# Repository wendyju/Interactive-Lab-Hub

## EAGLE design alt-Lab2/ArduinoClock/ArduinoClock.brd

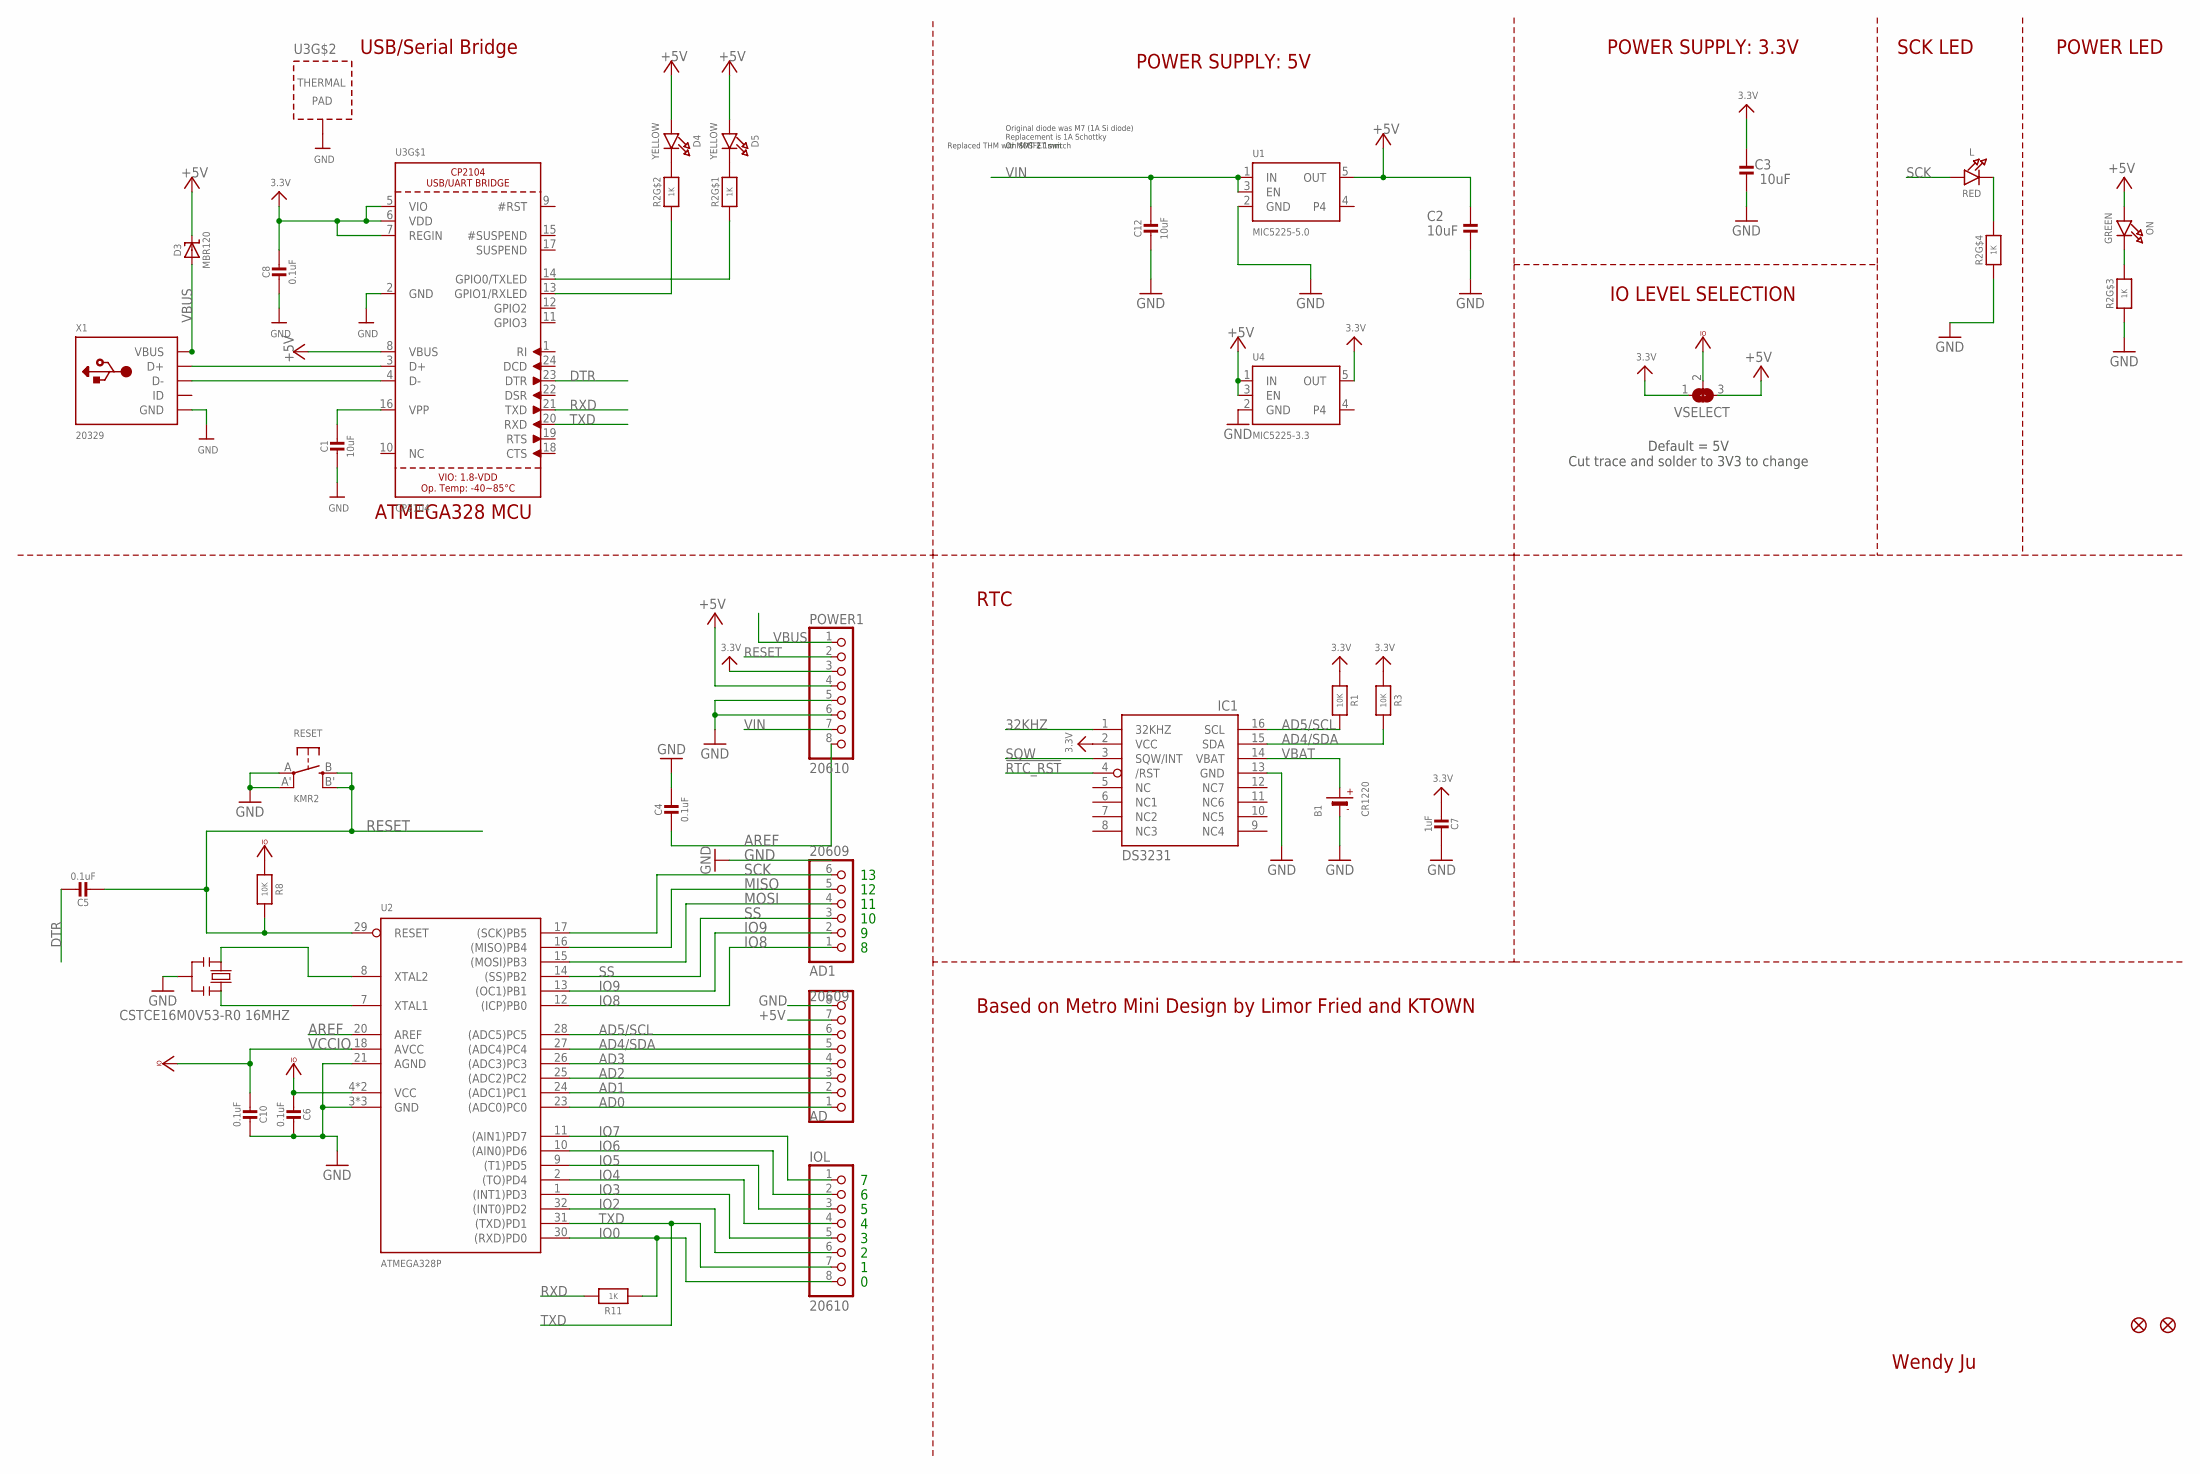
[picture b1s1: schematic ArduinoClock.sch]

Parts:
AD: 20609; 1X08_ROUND
AD1: 20609; 1X06_ROUND
B1: CR1220
C1, C2, C3, C12: 10uF; 0805-NO
C4, C6, C8, C10: 0.1uF; 0805-NO
C5: 0.1uF; _0805MP
C7: 1uF; 0805-NO
D3: MBR120; SOD-123
D4, D5: YELLOW; CHIPLED_0805_NOOUTLINE
FD1, FD2: FIDUCIAL""; FIDUCIAL_1MM
IC1: DS3231/SO; SO16W
IOL: 20610; 1X08_ROUND
L: RED; CHIPLED_0805_NOOUTLINE
ON: GREEN; CHIPLED_0805_NOOUTLINE
POWER1: 20610; 1X08_ROUND_70
R1, R3, R8: 10K; 0805-NO
R2: 1K; RESPACK_4X0603
R11: 1K; 0805-NO
RESET: KMR2; BTN_KMR2_4.6X2.8
U1: MIC5225-5.0; SOT23-5
U2: ATMEGA328P; MLF32-TH
U3: CP2104; QFN24_4MM_SMSC
U4: MIC5225-3.3; SOT23-5
VSELECT: SOLDERJUMPER_2WAY; SOLDERJUMPER_2WAY_OPEN_NOPASTE
X1: 20329; 4UCONN_20329_V2
Y2: CSTCE16M0V53-R0 16MHZ; RESONATOR

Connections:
3.3V: C3.2, C7.2, C8.1, IC1.2 (VCC), POWER1.3, R1.1, R3.1, U3.5 (VIO), U3.6 (VDD), U3.7 (REGIN), U4.5 (OUT), VSELECT.1
32KHZ: IC1.1 (32KHZ)
!RTC_RST: IC1.4 (/RST)
+5V: AD.7, C2.2, D3.C, D4.A, D5.A, ON.A, POWER1.4, U1.5 (OUT), U3.8 (VBUS), U4.1 (IN), U4.3 (EN), VSELECT.3
AD0: AD.1, U2.23 ((ADC0)PC0)
AD1: AD.2, U2.24 ((ADC1)PC1)
AD2: AD.3, U2.25 ((ADC2)PC2)
AD3: AD.4, U2.26 ((ADC3)PC3)
AD4/SDA: AD.5, IC1.15 (SDA), R3.2, U2.27 ((ADC4)PC4)
AD5/SCL: AD.6, IC1.16 (SCL), R1.2, U2.28 ((ADC5)PC5)
AREF: C4.2, POWER1.8, U2.20 (AREF)
DTR: C5.1, U3.23 (DTR)
GND: AD.8, B1.-, C1.2, C2.1, C3.1, C4.1, C6.1, C7.1, C8.2, C10.1, C12.2, IC1.13 (GND), POWER1.5, POWER1.6, R2.3 (1), R2.4 (1), RESET.A, RESET.A' (P1), U1.2 (GND), U2.3 (GND), U2.5 (GND), U2.21 (AGND), U2.TH (GND), U3.2 (GND), U3.THERM (TP), U4.2 (GND), X1.BASE@1 (GND), X1.BASE@2 (GND), X1.GND, X1.SPRT@1 (GND), X1.SPRT@2 (GND), X1.SPRT@3 (GND), X1.SPRT@4 (GND), Y2.2
IO0: IOL.8, R11.1, U2.30 ((RXD)PD0)
IO2: IOL.6, U2.32 ((INT0)PD2)
IO3: IOL.5, U2.1 ((INT1)PD3)
IO4: IOL.4, U2.2 ((TO)PD4)
IO5: IOL.3, U2.9 ((T1)PD5)
IO6: IOL.2, U2.10 ((AIN0)PD6)
IO7: IOL.1, U2.11 ((AIN1)PD7)
IO8: AD1.1, U2.12 ((ICP)PB0)
IO9: AD1.2, U2.13 ((OC1)PB1)
MISO: AD1.5, U2.16 ((MISO)PB4)
MOSI: AD1.4, U2.15 ((MOSI)PB3)
unnamed: L.C, R2.5 (2)
unnamed: ON.C, R2.6 (2)
unnamed: R2.1, U3.14 (GPIO0/TXLED)
unnamed: D4.C, R2.7 (2)
unnamed: D5.C, R2.8 (2)
unnamed: U3.3 (D+), X1.D+
unnamed: U3.4 (D-), X1.D-
unnamed: C1.1, U3.16 (VPP)
unnamed: R2.2 (1), U3.13 (GPIO1/RXLED)
RESET: C5.2, POWER1.2, R8.1, RESET.B (S), RESET.B' (S1), U2.29 (RESET)
RXD: R11.2, U3.21 (TXD)
SCK: AD1.6, L.A, U2.17 ((SCK)PB5)
SQW: IC1.3 (SQW/INT)
SS: AD1.3, U2.14 ((SS)PB2)
TXD: IOL.7, U2.31 ((TXD)PD1), U3.20 (RXD)
VBAT: B1.+$1 (+), IC1.14 (VBAT)
VBUS: D3.A, POWER1.1, X1.VBUS
VCCIO: C6.2, C10.2, R8.2, U2.4 (VCC), U2.6 (VCC), U2.18 (AVCC), VSELECT.2
VIN: C12.1, POWER1.7, U1.1 (IN), U1.3 (EN)
XTAL1: U2.7 (XTAL1), Y2.3
XTAL2: U2.8 (XTAL2), Y2.1

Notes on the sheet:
Wendy Ju
Original diode was M7 (1A Si diode) Replacement is 1A Schottky Or MOSFET switch
Replaced THM with SMT 2.1mm
POWER SUPPLY: 5V
USB/Serial Bridge
POWER SUPPLY: 3.3V
IO LEVEL SELECTION
POWER LED
ATMEGA328 MCU
SCK LED
Based on Metro Mini Design by Limor Fried and KTOWN
Default = 5V Cut trace and solder to 3V3 to change
RTC

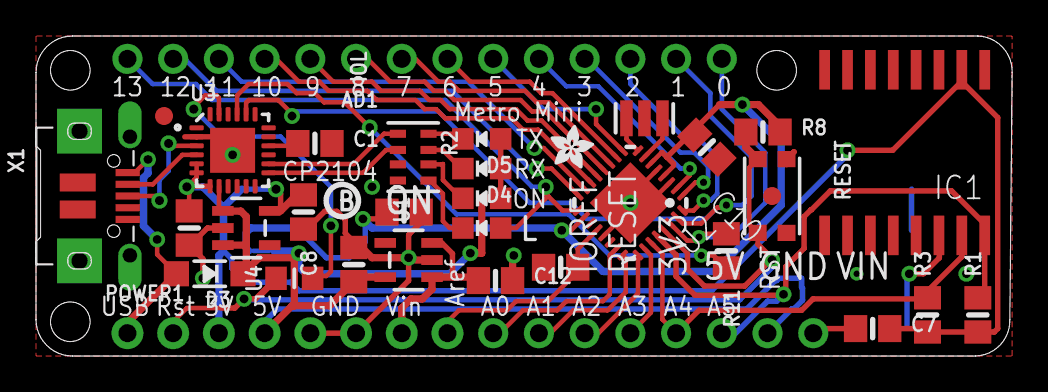
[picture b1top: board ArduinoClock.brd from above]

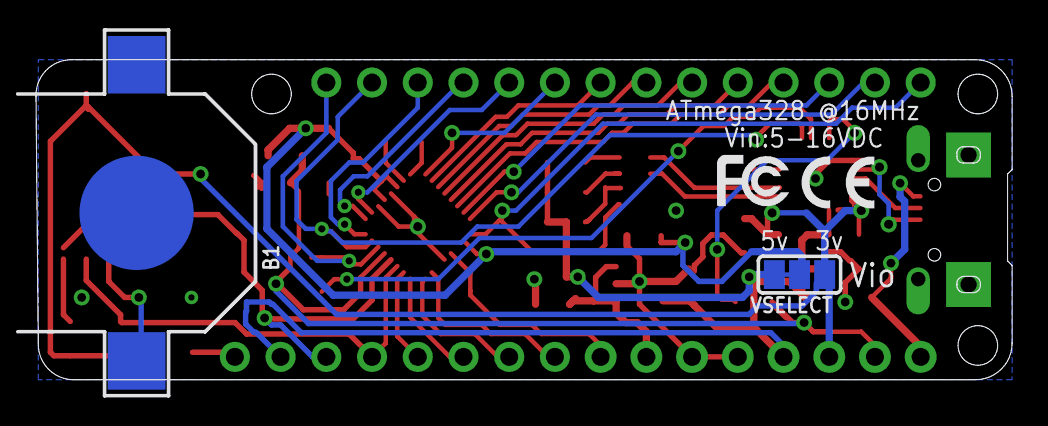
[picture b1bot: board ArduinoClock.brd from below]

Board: 2 copper layers, 54.2 x 17.8 mm, 40 parts (4 on the bottom side), 42 nets.

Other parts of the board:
U$4: PCBFEAT-REV-040
U$5: ADAFRUIT_2.5MM
U$12: SYMBOL_CE_TINY
U$14: SYMBOL_FCC_TINY

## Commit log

2020-09-14 fixed some ground planes and airwired
2020-09-15 adding new files
2020-09-15 almost ready, pre-bitmap
2020-09-15 passed design checks!
2020-09-15 fixed problems with placement.
2020-09-15 now with cool logo

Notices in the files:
parts and their libraries:
microbuilder: This work is placed in the public domain, and may be freely used for commercial and non-commercial work with the following conditions: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
